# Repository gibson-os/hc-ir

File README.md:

### Commands
| Number | Description      |
|--------|------------------|
| 0      | Send IR Command  |

Basic commands: [Module readme](src/hc-module/README.md)

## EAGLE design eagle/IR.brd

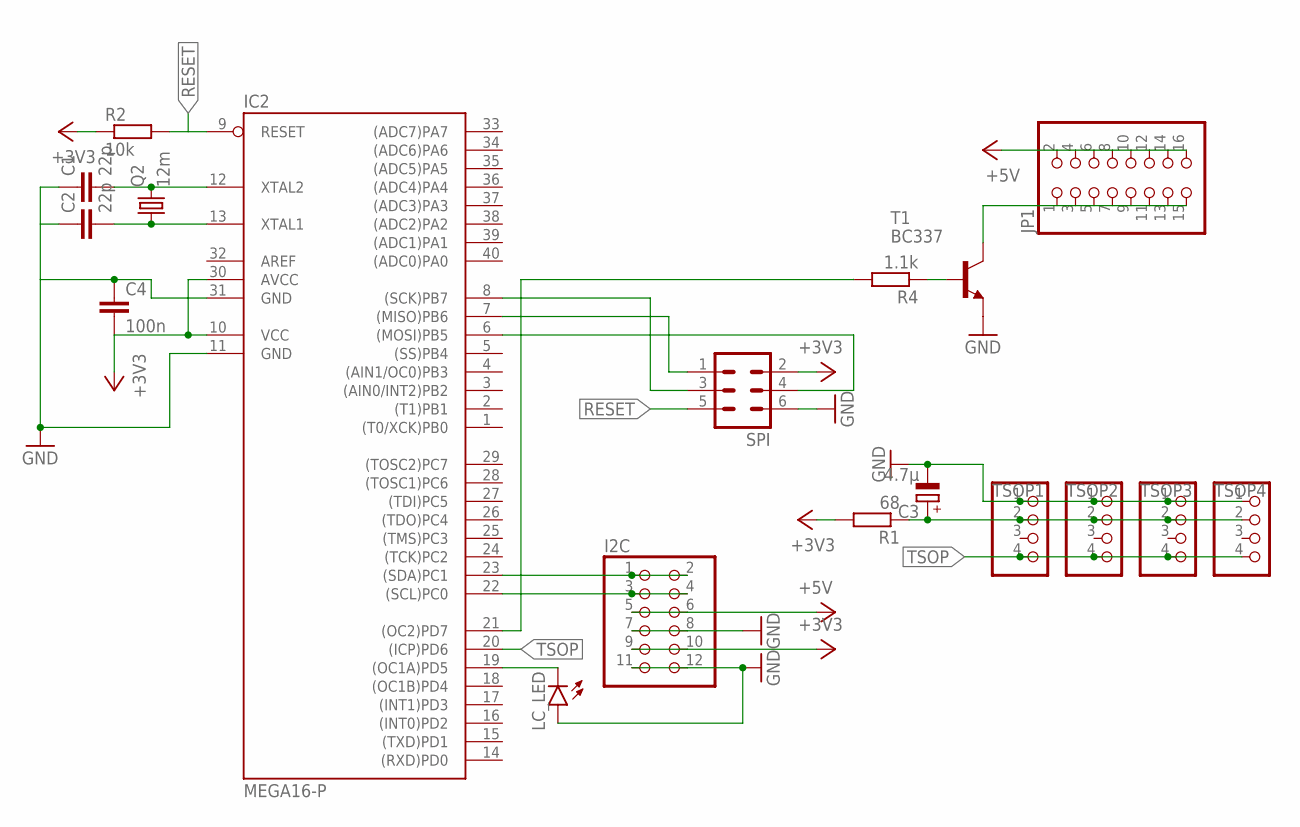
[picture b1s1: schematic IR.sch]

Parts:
C1, C2: 22p; C025-025X050
C3: 4.7µ; E1,8-4
C4: 100n; C025-025X050
I2C: PINHD-2X6; 2X06
IC2: MEGA16-P; DIL40
JP1: PINHD-2X8; 2X08
LC_LED: LED5MM
Q2: 12m; HC49/S
R1: 68; 0207/7
R2: 10k; 0207/7
R4: 1.1k; 0207/7
SPI: ML6
T1: BC337; TO92
TSOP1, TSOP2, TSOP3, TSOP4: PINHD-1X4; 1X04

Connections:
+3V3: C4.2, I2C.9, I2C.10, IC2.10 (VCC), IC2.30 (AVCC), R1.2, R2.1, SPI.2
+5V: I2C.5, I2C.6, JP1.2, JP1.4, JP1.6, JP1.8, JP1.10, JP1.12, JP1.14, JP1.16
GND: C1.1, C2.1, C3.-, C4.1, I2C.7, I2C.8, I2C.11, I2C.12, IC2.11 (GND), IC2.31 (GND), LC_LED.A, SPI.6, T1.1 (E), TSOP1.1, TSOP2.1, TSOP3.1, TSOP4.1
IO13: IC2.7 ((MISO)PB6), SPI.1
IO14: IC2.6 ((MOSI)PB5), SPI.4
unnamed: C2.2, IC2.13 (XTAL1), Q2.1
unnamed: IC2.21 ((OC2)PD7), R4.2
unnamed: R4.1, T1.2 (B)
unnamed: C1.2, IC2.12 (XTAL2), Q2.2
unnamed: JP1.1, JP1.3, JP1.5, JP1.7, JP1.9, JP1.11, JP1.13, JP1.15, T1.3 (C)
unnamed: IC2.19 ((OC1A)PD5), LC_LED.K (C)
unnamed: IC2.8 ((SCK)PB7), SPI.3
RESET: IC2.9 (RESET), R2.2, SPI.5
SCL: I2C.3, I2C.4, IC2.22 ((SCL)PC0)
SDA: I2C.1, I2C.2, IC2.23 ((SDA)PC1)
TSOP: IC2.20 ((ICP)PD6), TSOP1.4, TSOP2.4, TSOP3.4, TSOP4.4
TSOP_3_3: C3.+, R1.1, TSOP1.2, TSOP2.2, TSOP3.2, TSOP4.2

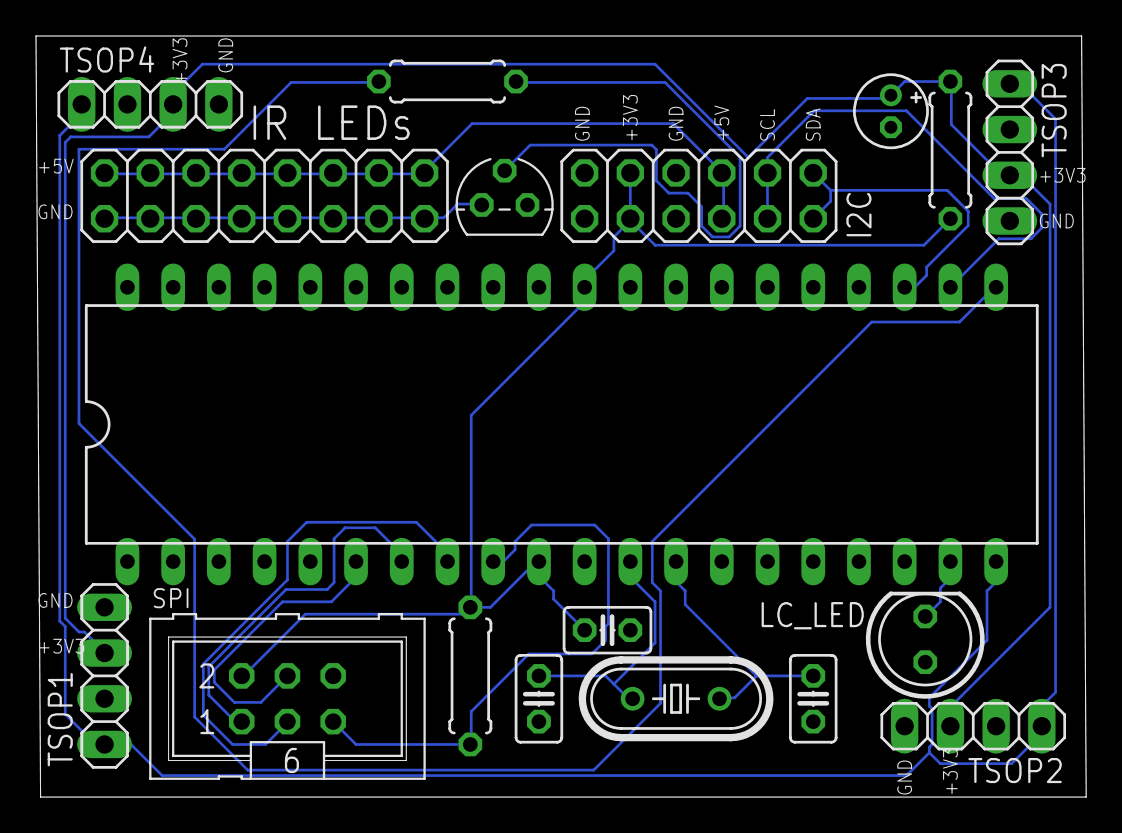
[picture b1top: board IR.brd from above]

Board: 2 copper layers, 58.3 x 42.3 mm, 18 parts (0 on the bottom side), 17 nets.

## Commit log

2022-12-18 Init commit
2022-12-18 Fix microchip studio project
2022-12-18 Remove ignored files
